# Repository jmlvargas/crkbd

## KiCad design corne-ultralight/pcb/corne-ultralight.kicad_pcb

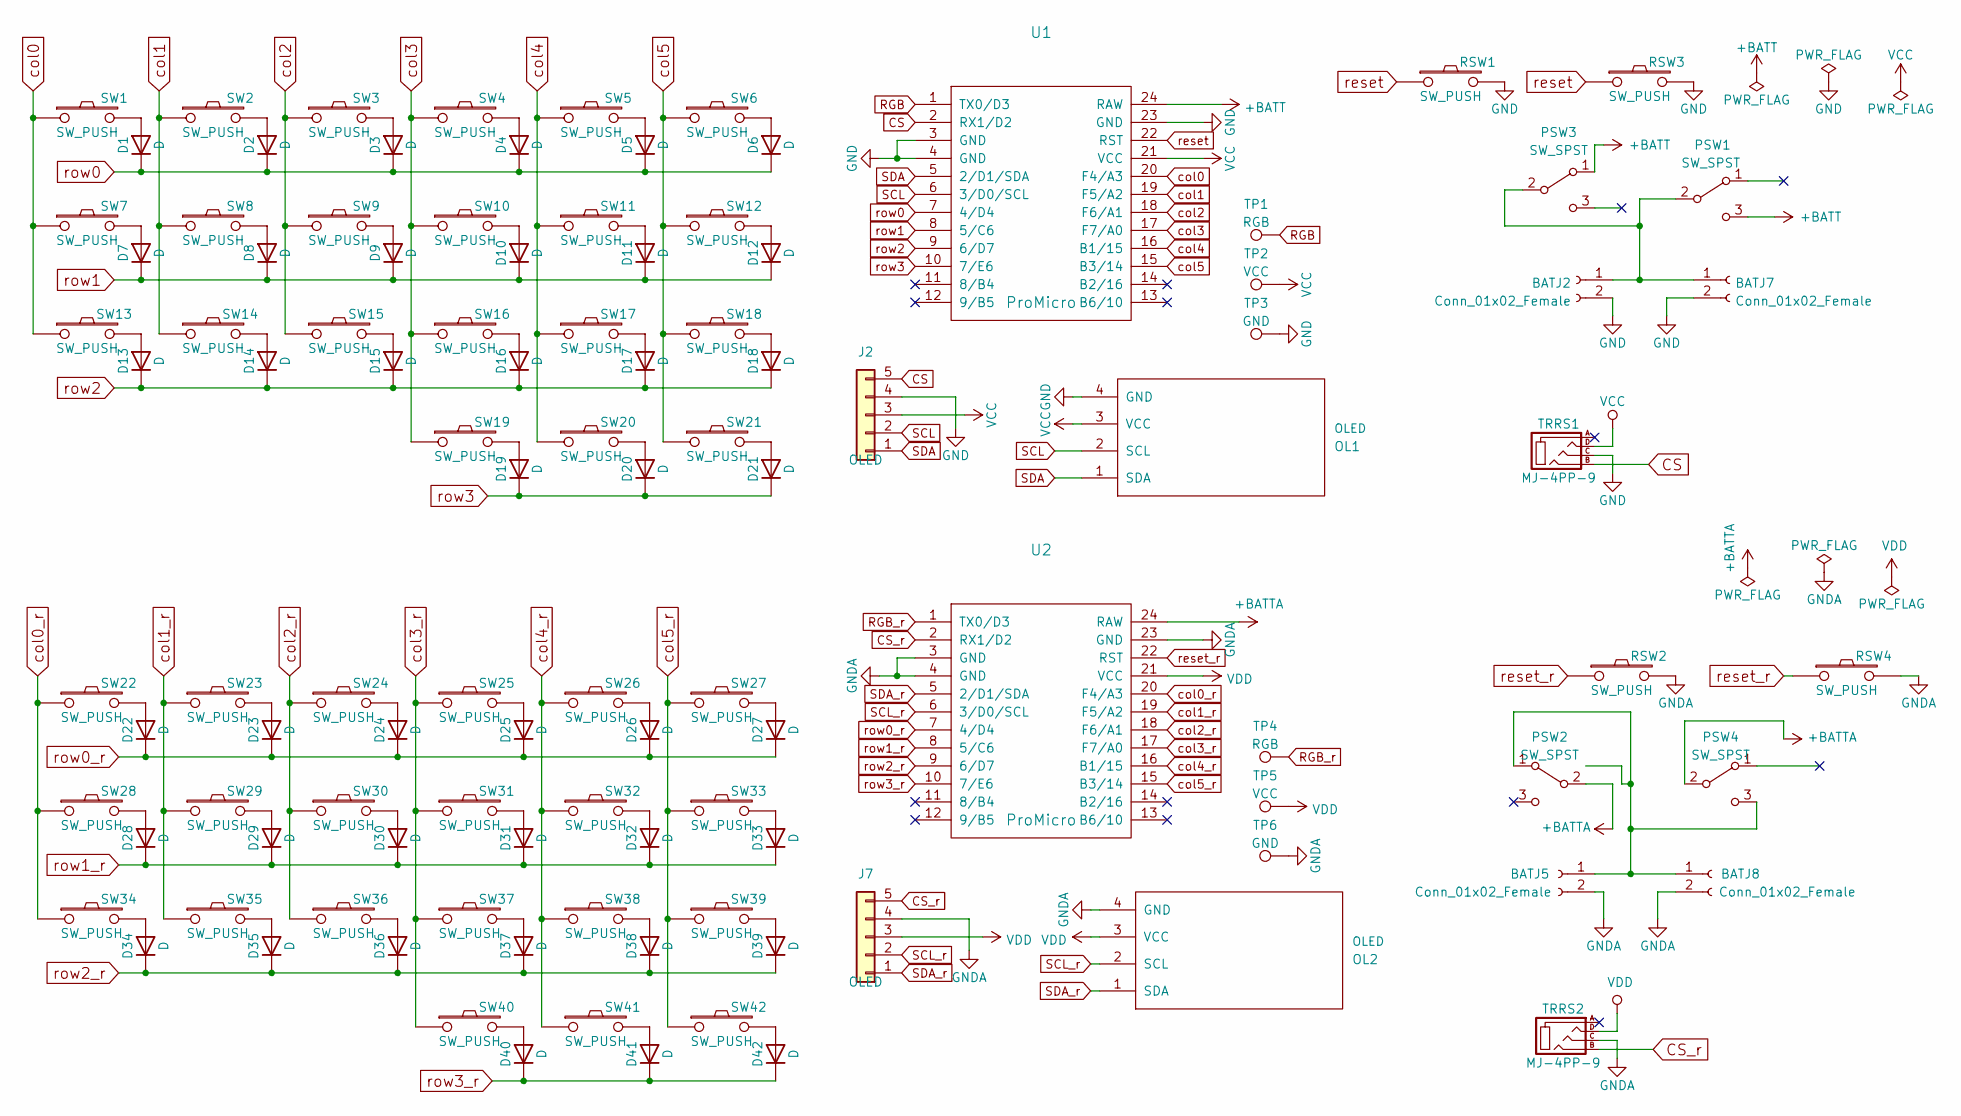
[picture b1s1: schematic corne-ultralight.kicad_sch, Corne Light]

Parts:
BATJ2, BATJ5, BATJ7, BATJ8: Conn_01x02_Female; JST_PH_S2B-PH-K_1x02_P2.00mm_Horizontal
D1, D2, D3, D4, D5, D6, D7, D8, D9, D10, D11, D12, D13, D14, D15, D16, D17, D18, D19, D20, D21, D22, D23, D24, D25, D26, D27, D28, D29, D30, D31, D32, D33, D34, D35, D36, D37, D38, D39, D40, D41, D42: D; D3_TH
J2, J7: OLED; nice_view_1side
OL1, OL2: OLED; OLED_1side
PSW1, PSW2, PSW3, PSW4: SW_SPST; SW_SPDT_PCM12_JX
RSW1, RSW2: SW_PUSH; ResetSW_1side
RSW3, RSW4: SW_PUSH; JxTreePinButton
SW1, SW2, SW3, SW4, SW5, SW6, SW7, SW8, SW9, SW10, SW11, SW12, SW13, SW14, SW15, SW16, SW17, SW18, SW19, SW20, SW22, SW23, SW24, SW25, SW26, SW27, SW28, SW29, SW30, SW31, SW32, SW33, SW34, SW35, SW36, SW37, SW38, SW39, SW40, SW41: SW_PUSH; gateron-ks27-choc-v1-mx
SW21, SW42: SW_PUSH; gateron-ks27-choc-v1-mx-1.5u
TP1, TP4: RGB; TestPoint_Pad_D1.5mm
TP2, TP5: VCC; TestPoint_Pad_D1.5mm
TP3, TP6: GND; TestPoint_Pad_D1.5mm
TRRS1, TRRS2: MJ-4PP-9; MJ-4PP-9_1side
U1, U2: ProMicro; ProMicro_v3

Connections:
+BATT: PSW1.3 (C), PSW3.1 (A), U1.24 (RAW)
+BATTA: PSW2.2 (B), PSW4.2 (B), U2.24 (RAW)
CS: J2.5, TRRS1.B, U1.2 (RX1/D2)
CS_r: J7.5, TRRS2.B, U2.2 (RX1/D2)
GND: BATJ2.2, BATJ7.2, J2.4, OL1.4 (GND), RSW1.2, RSW3.2, TP3.1, TRRS1.C, U1.3 (GND), U1.4 (GND), U1.23 (GND)
GNDA: BATJ5.2, BATJ8.2, J7.4, OL2.4 (GND), RSW2.2, RSW4.2, TP6.1, TRRS2.C, U2.3 (GND), U2.4 (GND), U2.23 (GND)
unnamed: BATJ2.1, BATJ7.1, PSW1.2 (B), PSW3.2 (B)
unnamed: BATJ5.1, BATJ8.1, PSW2.1 (A), PSW4.3 (C)
unnamed: D1.2 (A), SW1.2
unnamed: D2.2 (A), SW2.2
unnamed: D3.2 (A), SW3.2
unnamed: D4.2 (A), SW4.2
unnamed: D5.2 (A), SW5.2
unnamed: D6.2 (A), SW6.2
unnamed: D7.2 (A), SW7.2
unnamed: D8.2 (A), SW8.2
unnamed: D9.2 (A), SW9.2
unnamed: D10.2 (A), SW10.2
unnamed: D11.2 (A), SW11.2
unnamed: D12.2 (A), SW12.2
unnamed: D13.2 (A), SW13.2
unnamed: D14.2 (A), SW14.2
unnamed: D15.2 (A), SW15.2
unnamed: D16.2 (A), SW16.2
unnamed: D17.2 (A), SW17.2
unnamed: D18.2 (A), SW18.2
unnamed: D19.2 (A), SW19.2
unnamed: D20.2 (A), SW20.2
unnamed: D21.2 (A), SW21.2
unnamed: D22.2 (A), SW22.2
unnamed: D23.2 (A), SW23.2
unnamed: D24.2 (A), SW24.2
unnamed: D25.2 (A), SW25.2
unnamed: D26.2 (A), SW26.2
unnamed: D27.2 (A), SW27.2
unnamed: D28.2 (A), SW28.2
unnamed: D29.2 (A), SW29.2
unnamed: D30.2 (A), SW30.2
unnamed: D31.2 (A), SW31.2
unnamed: D32.2 (A), SW32.2
unnamed: D33.2 (A), SW33.2
unnamed: D34.2 (A), SW34.2
unnamed: D35.2 (A), SW35.2
unnamed: D36.2 (A), SW36.2
unnamed: D37.2 (A), SW37.2
unnamed: D38.2 (A), SW38.2
unnamed: D39.2 (A), SW39.2
unnamed: D40.2 (A), SW40.2
unnamed: D41.2 (A), SW41.2
unnamed: D42.2 (A), SW42.2
RGB: TP1.1, U1.1 (TX0/D3)
RGB_r: TP4.1, U2.1 (TX0/D3)
SCL: J2.2, OL1.2 (SCL), U1.6 (3/D0/SCL)
SCL_r: J7.2, OL2.2 (SCL), U2.6 (3/D0/SCL)
SDA: J2.1, OL1.1 (SDA), U1.5 (2/D1/SDA)
SDA_r: J7.1, OL2.1 (SDA), U2.5 (2/D1/SDA)
VCC: J2.3, OL1.3 (VCC), TP2.1, TRRS1.D, U1.21 (VCC)
VDD: J7.3, OL2.3 (VCC), TP5.1, TRRS2.D, U2.21 (VCC)
col0: SW1.1, SW7.1, SW13.1, U1.20 (F4/A3)
col0_r: SW22.1, SW28.1, SW34.1, U2.20 (F4/A3)
col1: SW2.1, SW8.1, SW14.1, U1.19 (F5/A2)
col1_r: SW23.1, SW29.1, SW35.1, U2.19 (F5/A2)
col2: SW3.1, SW9.1, SW15.1, U1.18 (F6/A1)
col2_r: SW24.1, SW30.1, SW36.1, U2.18 (F6/A1)
col3: SW4.1, SW10.1, SW16.1, SW19.1, U1.17 (F7/A0)
col3_r: SW25.1, SW31.1, SW37.1, SW40.1, U2.17 (F7/A0)
col4: SW5.1, SW11.1, SW17.1, SW20.1, U1.16 (B1/15)
col4_r: SW26.1, SW32.1, SW38.1, SW41.1, U2.16 (B1/15)
col5: SW6.1, SW12.1, SW18.1, SW21.1, U1.15 (B3/14)
col5_r: SW27.1, SW33.1, SW39.1, SW42.1, U2.15 (B3/14)
reset: RSW1.1, RSW3.1, U1.22 (RST)
reset_r: RSW2.1, RSW4.1, U2.22 (RST)
row0: D1.1 (K), D2.1 (K), D3.1 (K), D4.1 (K), D5.1 (K), D6.1 (K), U1.7 (4/D4)
row0_r: D22.1 (K), D23.1 (K), D24.1 (K), D25.1 (K), D26.1 (K), D27.1 (K), U2.7 (4/D4)
row1: D7.1 (K), D8.1 (K), D9.1 (K), D10.1 (K), D11.1 (K), D12.1 (K), U1.8 (5/C6)
row1_r: D28.1 (K), D29.1 (K), D30.1 (K), D31.1 (K), D32.1 (K), D33.1 (K), U2.8 (5/C6)
row2: D13.1 (K), D14.1 (K), D15.1 (K), D16.1 (K), D17.1 (K), D18.1 (K), U1.9 (6/D7)
row2_r: D34.1 (K), D35.1 (K), D36.1 (K), D37.1 (K), D38.1 (K), D39.1 (K), U2.9 (6/D7)
row3: D19.1 (K), D20.1 (K), D21.1 (K), U1.10 (7/E6)
row3_r: D40.1 (K), D41.1 (K), D42.1 (K), U2.10 (7/E6)

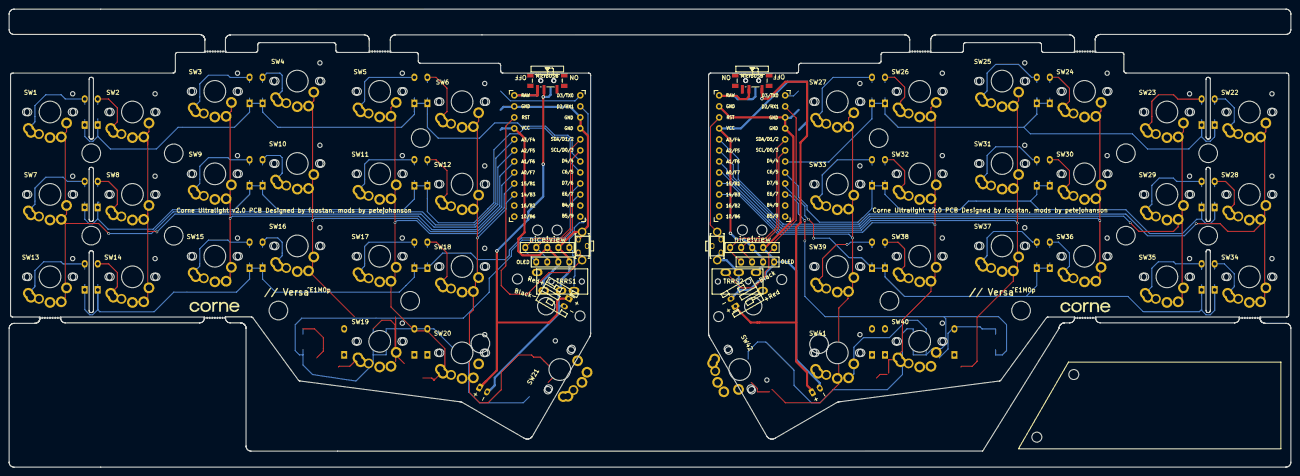
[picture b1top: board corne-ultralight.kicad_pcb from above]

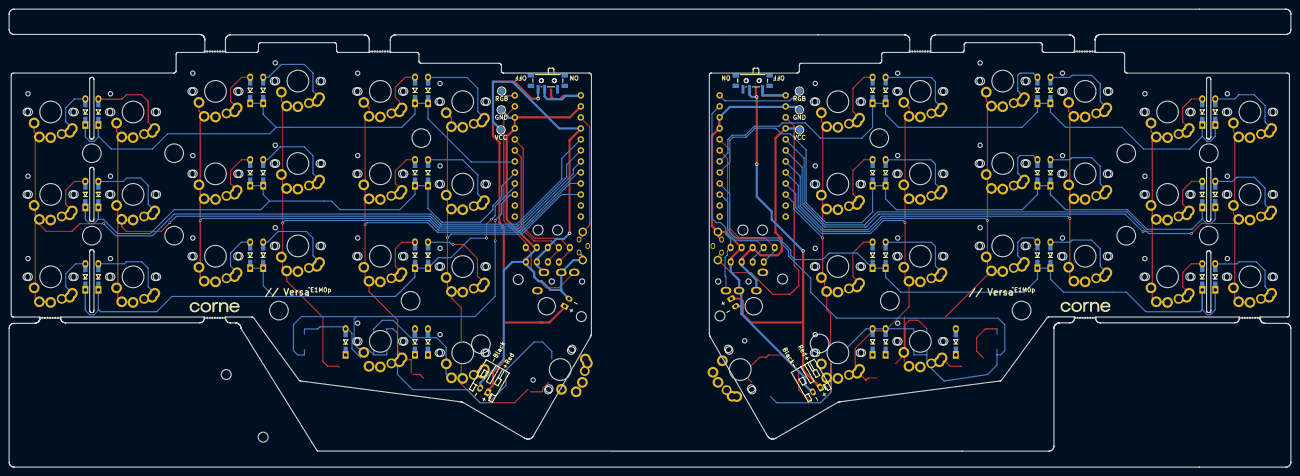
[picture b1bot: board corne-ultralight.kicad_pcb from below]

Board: 2 copper layers, 295.5 x 105.6 mm, 146 parts (74 on the bottom side), 80 nets.

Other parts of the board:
J5, J5#2, J5#3, J5#4, J5#5, J5#6, J5#7, J5#8: Breakaway_Tabs
Ref**: Val**; thread_m2
Ref**#2, Ref**#3, Ref**#4, Ref**#5, Ref**#6, Ref**#12, Ref**#13, Ref**#25, Ref**#26: Val**; thread_m2
Ref**#7, Ref**#8, Ref**#9, Ref**#10, Ref**#11, Ref**#14, Ref**#15, Ref**#16, Ref**#17, Ref**#18, Ref**#19, Ref**#20, Ref**#21, Ref**#22, Ref**#23, Ref**#24, Ref**#27, Ref**#28: Val**; spacer_m2

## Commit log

2025-01-05 Additional JST connectors and OLED in schematics
2025-01-05 Sockets fixed
2025-01-05 PCB updated with additional components
2025-01-05 Bottom JST connectors aligned
2025-01-05 OLED aligned
2025-01-05 All JST connectors routed
2025-01-05 Middle JST moved below the MCU
2025-01-05 Holes for battery cables
2025-01-05 BAT pines assignment fixes
2025-01-05 Left half rerouted
2025-01-06 All rerouted
2025-01-06 Some warnings and errors fixed
2025-01-06 Reinforced
2025-01-07 More fixes
2025-01-08 Squashed 'pcbs/common/kbd/' changes from c53bf51..1f12004
    1f12004 Update trrs footprint
    ce41334 Add keyswitch_hole
    git-subtree-dir: pcbs/common/kbd
    git-subtree-split: 1f12004a1c9714d0eabec4028c9ae4b259b41562
2025-01-08 Versa mods to support wired builds
2025-01-10 Routing fixes
2025-01-10 Additional JST
2025-01-10 Front mask for MCU pins
2025-01-10 Remove jumper label
2025-01-11 Reversed power switches
2025-01-11 Positioning fixes
2025-01-11 U1 position adjusted
2025-01-12 Bottom plate honeycomb design
2025-01-12 Bottom plate VersaKomb design
2025-01-13 Bottom plate, space for rubber feet
2025-01-21 Logo relocated
2025-01-22 Two small cable holes at the bottom edge of the visor
2025-01-22 Improved cable holes
2025-01-22 Bottom JST moved
2025-01-23 3d components
2025-01-25 tree pin reset btn WIP
2025-01-25 tree pin reset btn. done.
2025-01-25 oled is now perfectly aligned
2025-02-05 No choc to improve clearance
2025-02-06 Bottom plate: window for reset button
2025-02-06 Some wires fixed
2025-02-06 One batt connector less
2025-02-06 Batt labels fixed
2025-02-06 Rerouting
2025-02-08 chocs are back, rerouting to allow removing the hole contact
2025-02-08 Name restored
2025-02-09 MCU covers
2025-02-11 Tons of improvements
2025-04-11 Spaced
